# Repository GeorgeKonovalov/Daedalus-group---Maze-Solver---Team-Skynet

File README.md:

# Daedalus-group---Maze-Solver---Team-Skynet
2nd year project maze solver

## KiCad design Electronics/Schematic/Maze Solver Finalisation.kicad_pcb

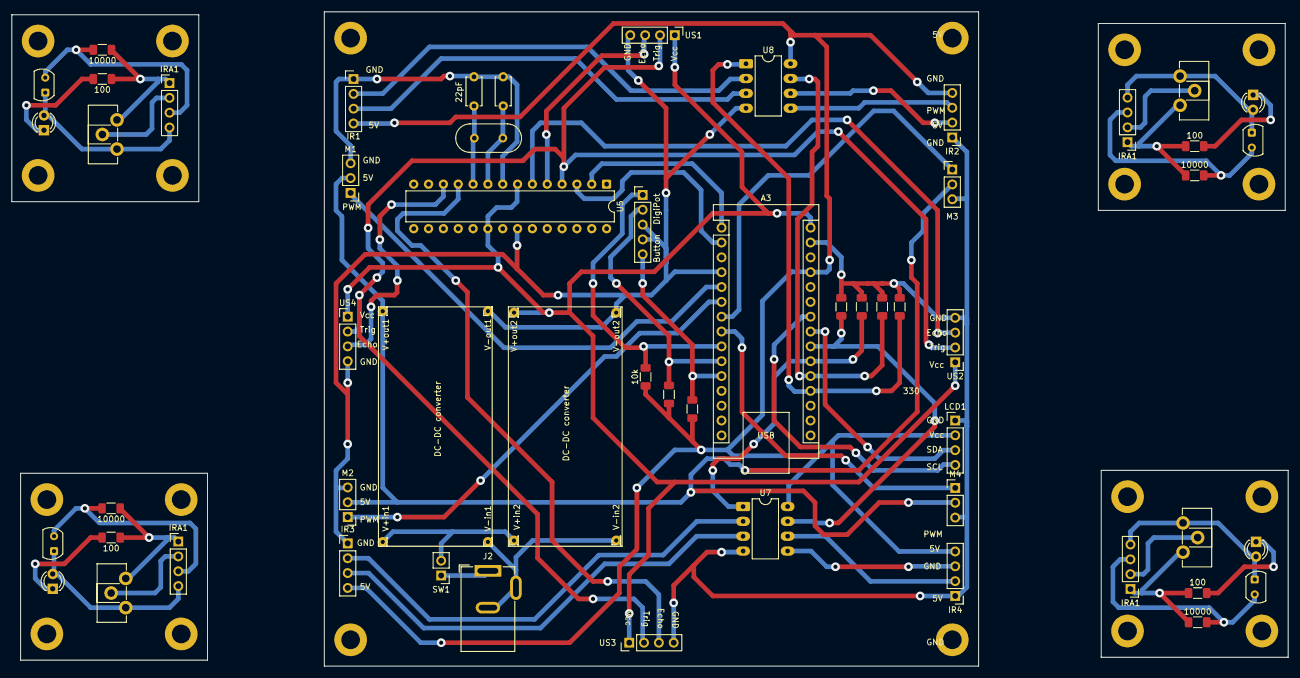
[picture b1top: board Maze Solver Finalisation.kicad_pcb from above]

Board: 2 copper layers, 218.5 x 112.0 mm, 62 parts (0 on the bottom side), 42 nets.

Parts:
A3: Arduino_Nano_RP2040_Connect; Arduino_Nano
C1, C2: 22pF; C_Disc_D4.7mm_W2.5mm_P5.00mm
D1, D1#2, D1#3, D1#4: D_Photo; Osram_SFH225
D2, D2#2, D2#3, D2#4: IR204A; LED_D3.0mm_IRBlack
DigiPot: PinHeader_1x05_P2.54mm_Vertical
IR1, IR2, IR3, IR4: Conn_01x04_Pin; PinHeader_1x04_P2.54mm_Vertical
IRA1, IRA1#2, IRA1#3, IRA1#4: Conn_01x04_Pin; PinHeader_1x04_P2.54mm_Vertical
J2: Power Supply; BarrelJack_GCT_DCJ200-10-A_Horizontal
LCD1: Conn_01x04_Pin; PinHeader_1x04_P2.54mm_Vertical
M1, M2, M3, M4: Motor_Servo; PinHeader_1x03_P2.54mm_Vertical
R2, R2#2, R2#3, R2#4: 10000; R_1206_3216Metric_Pad1.30x1.75mm_HandSolder
R3, R3#2, R3#3, R3#4: 100; R_1206_3216Metric_Pad1.30x1.75mm_HandSolder
R7, R8, R9: 10k; R_1206_3216Metric_Pad1.30x1.75mm_HandSolder
R12, R13, R25, R26: 330; R_1206_3216Metric_Pad1.30x1.75mm_HandSolder
RV1, RV1#2, RV1#3, RV1#4: R_Potentiometer; Potentiometer_ACP_CA9-H2,5_Horizontal
SW1: SW_SPST; PinHeader_1x02_P2.54mm_Vertical
U5: ATmega328P-P; DIP-28_W7.62mm
U7, U8: LM358; DIP-8_W7.62mm_LongPads
US1, US2, US3, US4: Conn_01x04_Pin; PinHeader_1x04_P2.54mm_Vertical
V+in1, V+in2: Conn_01x01_Pin; PinHeader_1x01_P1.00mm_Vertical
V+out1, V+out2: Conn_01x01_Pin; PinHeader_1x01_P1.00mm_Vertical
V-in1, V-in2: Conn_01x01_Pin; PinHeader_1x01_P1.00mm_Vertical
V-out1, V-out2: Conn_01x01_Pin; PinHeader_1x01_P1.00mm_Vertical
Y1: Crystal; Crystal_HC49-4H_Vertical

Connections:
+5V: A3.30 (VIN), U5.7 (VCC), U5.20 (AVCC), US1.1, US2.1, US3.1, US4.1, V+out2.1
GND: A3.4 (GND), A3.29 (GND), C1.2, C2.1, DigiPot.3, DigiPot.4, IR1.1, IR2.1, IR3.1, IR4.1, LCD1.1, M1.3 (-), M2.3 (-), M3.3 (-), M4.3 (-), R12.2, R13.2, R25.2, R26.2, U5.8 (GND), U5.22 (GND), U7.4 (V-), U8.4 (V-), US1.4, US2.4, US3.4, US4.4, V-out1.1, V-out2.1
unnamed: A3.19 (A0), R26.1, U8.1
unnamed: A3.20 (A1), R25.1, U8.7
unnamed: A3.21 (A2), R12.1, U7.1
unnamed: A3.22 (A3), R13.1, U7.7
unnamed: A3.2 (D0/RX), U5.3 (PD1)
unnamed: A3.1 (D1/TX), U5.2 (PD0)
unnamed: A3.5 (D2), M1.1 (PWM)
unnamed: A3.6 (D3), M2.1 (PWM)
unnamed: A3.7 (D4), M3.1 (PWM)
unnamed: A3.8 (D5), M4.1 (PWM)
unnamed: A3.9 (D6), DigiPot.1, R9.1
unnamed: A3.10 (D7), DigiPot.2, R8.1
unnamed: A3.11 (D8), DigiPot.5, R7.1
unnamed: A3.24 (SCL/A5), LCD1.4
unnamed: A3.23 (SDA/A4), LCD1.3
unnamed: A3.27 (VUSB/5V), IR1.4, IR2.4, IR3.4, IR4.4, LCD1.2, R7.2, R8.2, R9.2, U7.8 (V+), U8.8 (V+)
unnamed: D1.2 (A), D1#2.2 (A), D1#3.2 (A), D1#4.2 (A), IRA1.3, IRA1#2.3, IRA1#3.3, IRA1#4.3, R2.1, R2#2.1, R2#3.1, R2#4.1
unnamed: D1.1 (K), D1#2.1 (K), D1#3.1 (K), D1#4.1 (K), D2.2 (A), D2#2.2 (A), D2#3.2 (A), D2#4.2 (A), IRA1.4, IRA1#2.4, IRA1#3.4, IRA1#4.4, RV1.1, RV1#2.1, RV1#3.1, RV1#4.1
unnamed: D2.1 (K), D2#2.1 (K), D2#3.1 (K), D2#4.1 (K), R3.1, R3#2.1, R3#3.1, R3#4.1
unnamed: IR1.2, U8.2 (-)
unnamed: IR1.3, U8.3 (+)
unnamed: IR2.2, U8.6 (-)
unnamed: IR2.3, U8.5 (+)
unnamed: IR3.2, U7.2 (-)
unnamed: IR3.3, U7.3 (+)
unnamed: IR4.2, U7.6 (-)
unnamed: IR4.3, U7.5 (+)
unnamed: IRA1.1, IRA1#2.1, IRA1#3.1, IRA1#4.1, R2.2, R2#2.2, R2#3.2, R2#4.2, R3.2, R3#2.2, R3#3.2, R3#4.2, RV1.3, RV1#2.3, RV1#3.3, RV1#4.3
unnamed: IRA1.2, IRA1#2.2, IRA1#3.2, IRA1#4.2, RV1.2, RV1#2.2, RV1#3.2, RV1#4.2
unnamed: M1.2 (+), M2.2 (+), M3.2 (+), M4.2 (+), V+out1.1
unnamed: J2.1, SW1.1 (A)
unnamed: SW1.2 (B), V+in1.1, V+in2.1
unnamed: U5.4 (PD2), US1.2, US2.2, US3.2, US4.2
unnamed: U5.5 (PD3), US1.3
unnamed: U5.6 (PD4), US2.3
unnamed: U5.11 (PD5), US3.3
unnamed: U5.12 (PD6), US4.3
unnamed: C1.1, U5.9 (XTAL1/PB6), Y1.2
unnamed: C2.2, U5.10 (XTAL2/PB7), Y1.1
unnamed: J2.2, J2.3, V-in1.1, V-in2.1

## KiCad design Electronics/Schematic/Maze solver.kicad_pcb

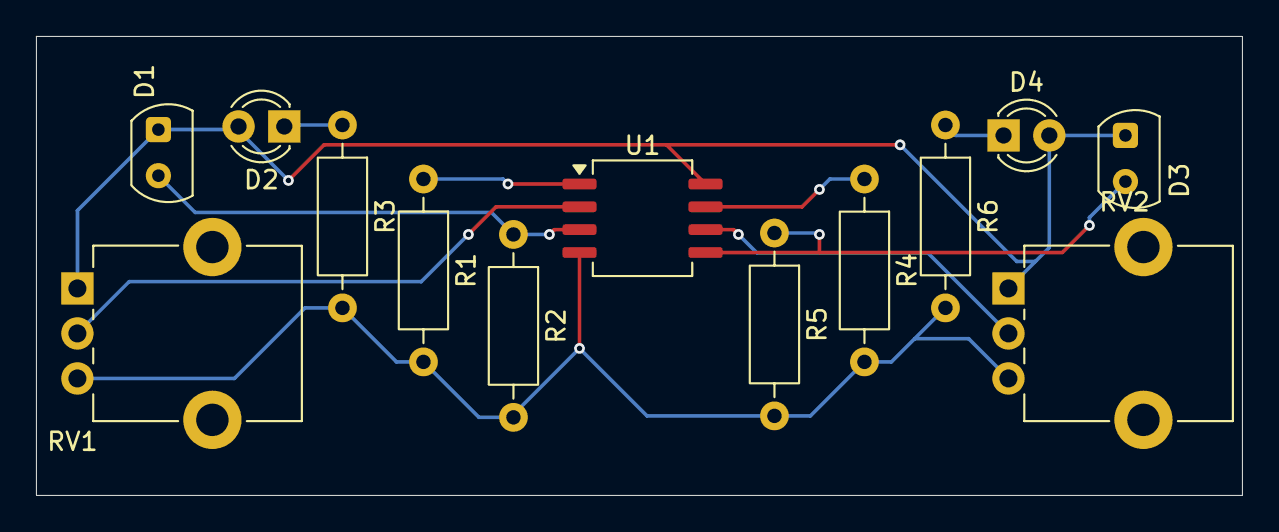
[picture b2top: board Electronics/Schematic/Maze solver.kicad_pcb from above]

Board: 2 copper layers, 67.0 x 25.5 mm, 13 parts (0 on the bottom side), 10 nets.

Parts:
D1, D3: D_Photo; Osram_SFH225
D2, D4: IR204A; LED_D3.0mm_IRBlack
R1, R4: 330; R_Axial_DIN0207_L6.3mm_D2.5mm_P10.16mm_Horizontal
R2, R5: 10000; R_Axial_DIN0207_L6.3mm_D2.5mm_P10.16mm_Horizontal
R3, R6: 100; R_Axial_DIN0207_L6.3mm_D2.5mm_P10.16mm_Horizontal
RV1, RV2: R_Potentiometer; Potentiometer_Alpha_RD901F-40-00D_Single_Vertical_CircularH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
U1: LM358; SOIC-8_5.3x6.2mm_P1.27mm

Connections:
+5V: D1.1 (K), D2.2 (A), D3.1 (K), D4.2 (A), RV1.1, RV2.1, U1.8 (V+)
GND: R1.2, R2.2, R3.2, R4.2, R5.2, R6.2, RV1.3, RV2.3, U1.4 (V-)
unnamed: D1.2 (A), R2.1, U1.3 (+)
unnamed: D2.1 (K), R3.1
unnamed: D3.2 (A), R5.1, U1.5 (+)
unnamed: D4.1 (K), R6.1
unnamed: RV1.2, U1.2 (-)
unnamed: RV2.2, U1.6 (-)
Vout 1: R1.1, U1.1
Vout 2: R4.1, U1.7

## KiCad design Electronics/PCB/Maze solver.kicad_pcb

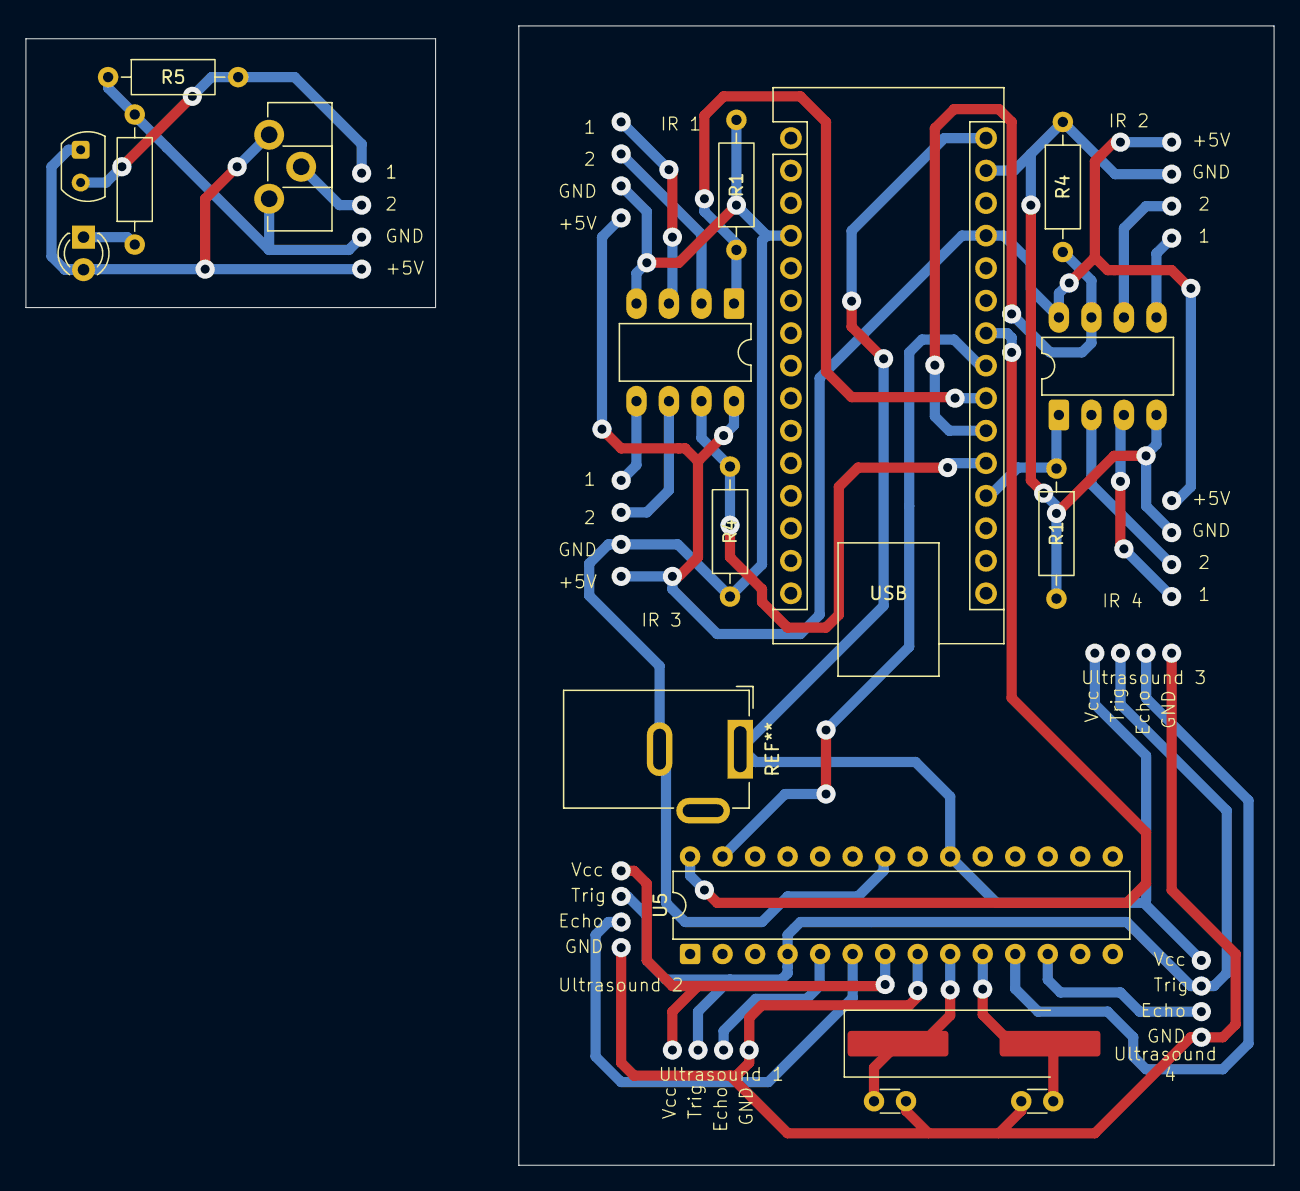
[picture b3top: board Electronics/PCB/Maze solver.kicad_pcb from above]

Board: 2 copper layers, 97.5 x 89.0 mm, 12 parts (0 on the bottom side), 8 nets.

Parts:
A1: Arduino_Nano_RP2040_Connect; Arduino_Nano
D3: D_Photo; Osram_SFH225
D4: IR204A; LED_D3.0mm_IRBlack
R1, R1#2, R4, R4#2: 330; R_Axial_DIN0207_L6.3mm_D2.5mm_P10.16mm_Horizontal
R5: 10000; R_Axial_DIN0207_L6.3mm_D2.5mm_P10.16mm_Horizontal
R6: 100; R_Axial_DIN0207_L6.3mm_D2.5mm_P10.16mm_Horizontal
U1, U1#2: LM358; DIP-8_W7.62mm_LongPads
U5: ATmega328P-P; DIP-28_W7.62mm

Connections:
GND: R1.2, R4.2, U1.4 (V-)
IR 1: A1.22 (A3), R1#2.1, U1#2.1
IR 2: A1.20 (A1), R4.1, R4#2.1, U1.7, U1#2.7
IR 4: A1.21 (A2), R1.1, U1.1
Ultrasound 1 GND: A1.4 (GND), A1.29 (GND), R1#2.2, R4#2.2, U1#2.4 (V-), U5.8 (GND), U5.22 (GND)
Ultrasound 1 Vcc: A1.27 (VUSB/5V), U1#2.8 (V+), U5.7 (VCC), U5.20 (AVCC)
i2C Clock: A1.24 (SCL/A5), U5.28 (PC5)
i2C Data: A1.23 (SDA/A4), U5.27 (PC4)

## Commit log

2025-11-24 Servo from GrabCAD
2025-11-24 Info added to show the new files
2025-11-24 Files structure is added by including info txt files
2025-11-28 mechanum_wheel_update
2025-12-01 Implement DFS maze solver in C
    This file implements a depth-first search (DFS) maze solver in C. It includes functions for navigating a maze, handling user input for starting position and direction, and backtracking when necessary.
2025-12-01 Add event-based DFS maze solver implementation
    This file implements an event-based depth-first search (DFS) maze solver for a robot using IR sensors. It includes functions for navigating the maze, classifying locations, and managing a stack for b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
2025-12-01 Add files via upload
    contains video of onboard delay adjuster
2026-01-22 Create ~$ttery_Cap.m3~
2026-01-22 Create ~$canum_wheel_60mm_model_aprox.m3~
2026-01-22 Create ~$sembly.a3~
2026-01-27 Update ~$ttery_Cap.m3~
2026-01-27 Update ~$sembly.a3~
2026-01-27 Create ~$wer_Base.m3~
2026-01-27 Update ~$canum_wheel_60mm_model_aprox.m3~
2026-01-27 Create ~$iven_Gear.m3~
2026-01-27 Create ~$arbox_Housing_Cap.m3~
2026-01-27 Create ~$arbox_Housing.m3~
2026-01-27 Create ~$ad_Gear_Cap.m3~
2026-01-27 Create ~$ad Gear.m3~
2026-01-27 Create ~$ddle_1mm.m3~
2026-01-27 Create ~$sembly48mm.a3~
2026-01-27 Create ~$sembly_Test.a3~
2026-02-01 Update ~$wer_Base.m3~
2026-02-01 Update ~$iven_Gear.m3~
2026-02-01 Update ~$arbox_Housing_Cap.m3~
2026-02-01 Update ~$arbox_Housing.m3~
2026-02-01 Create ~$ar_Lead_ASM.a3~
2026-02-01 Update ~$ad_Gear_Cap.m3~
2026-02-01 Update ~$ad Gear.m3~
2026-02-01 Create ~$rallax-Servo-Horn.m3~
2026-02-01 Update ~$sembly_Test.a3~
2026-02-01 Update ~$sembly48mm.a3~
2026-02-01 Update ~$ddle_1mm.m3~
2026-02-02 Updated PCB
2026-02-08 Model Update + NEW PRINTS
    Kamal, please, read the instruction about the prints
2026-02-08 STL update (additional screws)
    Screw holes are added for better rigidity of the sensor located on the Gearbox
2026-02-08 Istruction update
2026-02-12 Uploaded Finalised Schematic Draft
2026-02-12 Not yet ready keyboard control
2026-02-12 Wheel test code
    All servos zero states are tuned
2026-02-14 tuned_wasd update
    5V version
    Most probably should be updated after the switch to the higher voltage
2026-02-17 Add files via upload
    test code for uart connection
2026-02-22 Uploaded verified schematic and PCB
2026-02-22 Create IR Gerber
2026-02-22 Create info
2026-02-22 Uploaded IR Gerber files
2026-02-22 Uploaded Main Gerber Files
2026-02-25 PCB holders
    PCB holder
    Ultrasonic holder
    Idea for adjusted gearbox
2026-02-25 Upadate pCB
2026-03-02 1.85mm_version_of_omni
2026-03-06 Rover Systematic layout update (for CDR)
2026-03-15 LCD + Digipot holder
2026-04-03 TEST_DIGIPOT
2026-04-03 Add files via upload
    final code for atmega328p
2026-04-04 Menu_Test
2026-04-05 TEST Voltage on RP2040
    Wasn't upload on my PC
2026-04-05 Menu v.2
    Update of Menu code
2026-04-06 Model update
2026-04-06 Setup+Loop Menu updated
    See the menu/Menu_start_loop
2026-04-06 menu update
2026-04-07 Menu_update
2026-04-07 maze algorith test, no motors
2026-04-07 LED Scoop + Renewed AtmegaCode + Menu Update
2026-04-07 test algorithm without motors
2026-04-08 health test for motors
2026-04-08 fixed servo function
2026-04-08 final code without start stop and runs
2026-04-08 coridor test
2026-04-08 corridor test in folder
2026-04-08 added dead end to corridor test
2026-04-08 Merged code released
    Menu (start) with parameters transfer to corridor
2026-04-08 updated gains on pid corridor test
2026-04-08 swapped north south ultrasound values
2026-04-09 New PID initial values
2026-04-09 WiFi sampled
2026-04-09 inverted motor response
2026-04-09 flipped east west sensors
2026-04-09 changed drive function
2026-04-10 Full-testы
2026-04-11 full-test update
    new tests and IR validation event triggering
2026-04-11 new test code for averaged ultrasound sensors
2026-04-11 new nano recieve test with averaging and uncertainty handling
2026-04-11 added og maze solver demo code
2026-04-11 test 10 (renewed logic + PID for single wall)
2026-04-11 New versions
    v.11 and v.12 detects really badly (v.9 is the best currently)
2026-04-11 Digital twin updated
2026-04-13 v.18 + symmetric PID trial
    PID based on magnitude and sign
2026-04-13 revised drive to fix gain implementation
2026-04-13 New logic
2026-04-13 New Tunings
2026-04-13 new drive code and fixed all gains to 1
2026-04-13 new layout of settings
    +explaination table for functions
2026-04-13 Create test_full_v24.ino
    New Architecture trial
2026-04-14 update
    beginning of IMU implementation
    new folder
    renewed logic
2026-04-14 IMU implemented
    IMU implemented (badly) - better without one
2026-04-14 Tests update IMU
    IMU fixed attempt
2026-04-14 PID checks continuation
2026-04-15 reorganisation and menu update and fixed logic
2026-04-16 motors settings update
    reverse speed is cancelled for control
    + overall speed update
2026-04-16 Suspension test files - Models
    New test for the suspension CAD files
2026-04-16 timing optimisation
2026-04-16 changes in directions
    messed up sensors 180 degrees
2026-04-17 PID test + menu fixed glitches
    v.48 - normalised PID test
    v.47 - fixed menu glitches
2026-04-18 tuned PID + fixed IMU
2026-04-19 1/2 wall PID, IMU lateral PID, Event recognition changes
    Finish after T-junction
2026-04-20 assembled CAD + front compensation code
2026-04-22 new code and back to previous
2026-04-22 new code works not well
2026-04-22 final version untuned
